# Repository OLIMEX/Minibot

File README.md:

# Minibot
Small Educational Robot programmable with Arduino, with two motors and sensors to follow line or escape from labyrinth

## LICENSE
* Software License is GPL3
* Hardware License is Apache 2.0
* Documentation License is CC-BY-SA3.0 (https://creativecommons.org/licenses/by-sa/3.0/)

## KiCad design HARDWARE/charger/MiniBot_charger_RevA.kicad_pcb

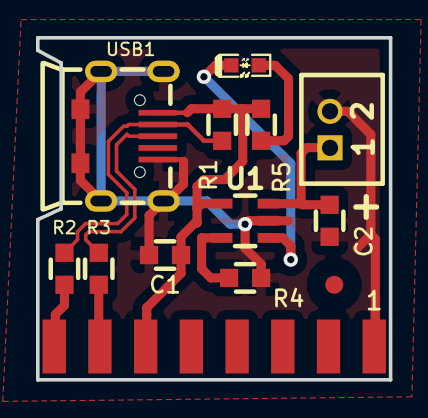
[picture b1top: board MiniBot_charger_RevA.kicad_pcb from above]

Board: 2 copper layers, 19.6 x 19.0 mm, 13 parts (0 on the bottom side), 10 nets.

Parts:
BAT_CON1: BAT_CON; LIPO_BAT_VERTICAL_DW02S
C1, C2: 2.2uF/6.3V; C_0603_5MIL_DWS
CON1: CON8; SIP8_SMD
LED1: LED_Small; LED_0603_KA
R1: 1.5K; R_0603_5MIL_DWS
R2, R3: 22R; R_0603_5MIL_DWS
R4: 13K_1%; R_0603_5MIL_DWS
R5: 10K; R_0603_5MIL_DWS
Ref*: Val**; Fiducial1x3_transp
U1: BL4054B-42TPRN(SOT23-5); SOT-23-5
USB1: USB-uicro; USB-MICRO_MISB-SWMM-5B_LF

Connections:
/D_N: R1.2, R2.2, USB1.2
/D_P: R3.2, USB1.3
GND: BAT_CON1.2, C1.2, C2.2, CON1.1, R4.2, U1.2, USB1.0, USB1.5
unnamed: BAT_CON1.1, C2.1, U1.3
unnamed: C1.1, CON1.6, R1.1, R5.1, U1.4, USB1.1
unnamed: CON1.7, R3.1
unnamed: CON1.8, R2.1
unnamed: LED1.1, U1.1
unnamed: LED1.2, R5.2
unnamed: R4.1, U1.5

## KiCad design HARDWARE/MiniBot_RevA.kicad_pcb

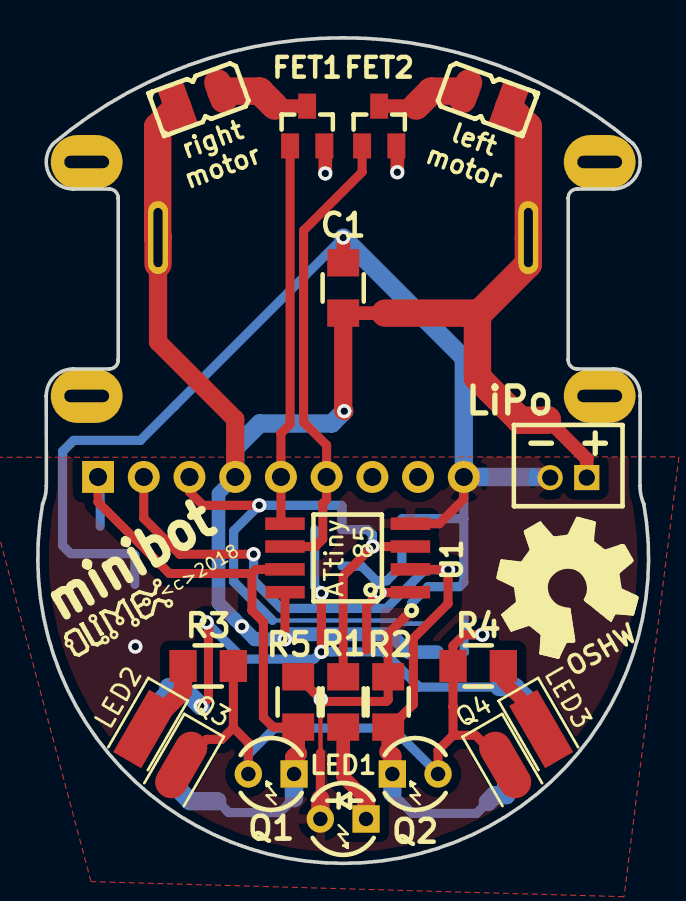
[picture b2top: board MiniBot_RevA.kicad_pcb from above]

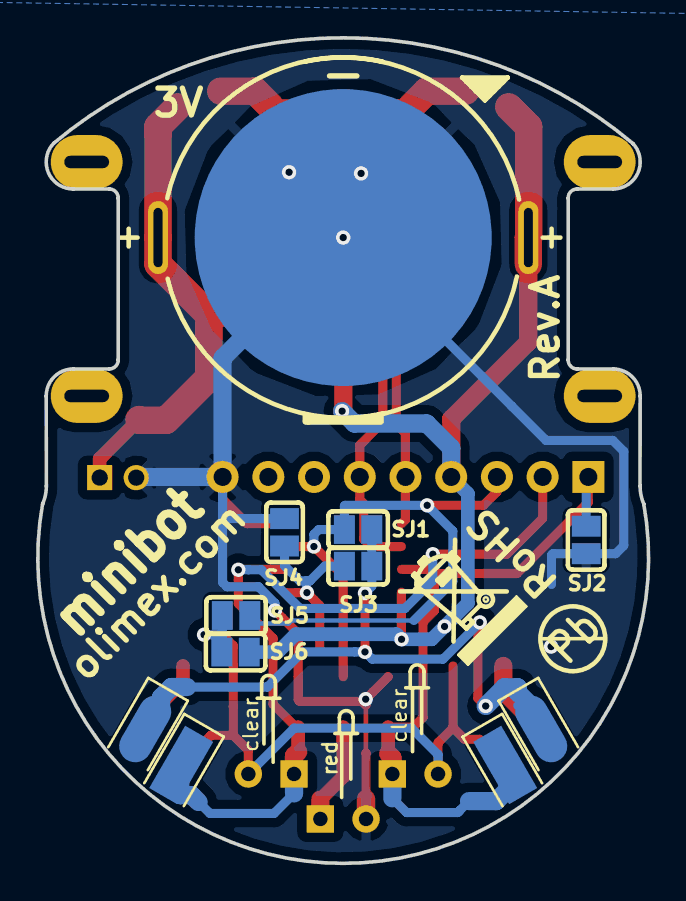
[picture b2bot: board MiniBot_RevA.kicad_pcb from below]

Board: 2 copper layers, 33.9 x 45.9 mm, 27 parts (7 on the bottom side), 15 nets.

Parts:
BAT1: Battery; CR2032H_PTH
BAT_CON2: BAT_CON; LIPO_BAT_VERTICAL_DW02S
C1: C_Small; C_1206_5MIL_DWS
CON1: LEFT MOTOR; MIC-TERES
CON2: RIGHT MOTOR; MIC-TERES
EXT1: nRF; HN1x9
FET1, FET2: WNM2016-3; SOT23
LED1: RED 3mm; LED-3mm-PTH-KA
LED2, LED3: RED 3mm; LED-EDGE
Q1, Q2: L342; LED-3mm-PTH-KA
Q3, Q4: L342; L34x-EDGE
R1, R3, R4: 1K; R_1206_5MIL_DWS
R2, R5: 3.3K; R_1206_5MIL_DWS
SJ1: leds_join; SJ
SJ2: arduino; SJ
SJ3, SJ5, SJ6: eco; SJ
SJ4: reset; SJ
U1: ATTINY85-20PU; SO-8_208mil

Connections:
/BAT+: BAT1.1, BAT_CON2.1, C1.1, CON1.1, CON2.1, EXT1.4, SJ6.2, U1.8
/FLED: SJ3.1, SJ4.1, U1.1
/LMOTOR: EXT1.6, FET2.1, U1.6
/LSENSE: EXT1.2, Q2.1, Q4.1, R2.1, U1.2
/RMOTOR: EXT1.5, FET1.1, U1.5
/RSENSE: EXT1.1, Q1.1, Q3.1, R5.1, SJ2.2, U1.7
/SLED: EXT1.3, R1.1, SJ1.1, SJ5.2, U1.3
GND: BAT1.2, BAT_CON2.2, C1.2, EXT1.9, FET1.2, FET2.2, LED1.1, R2.2, R5.2, SJ2.1, SJ4.2, U1.4
unnamed: CON1.2, FET2.3
unnamed: CON2.2, FET1.3
unnamed: LED1.2, R1.2
unnamed: LED2.1, LED3.1, SJ1.2, SJ3.2
unnamed: LED2.2, R3.2
unnamed: LED3.2, R4.2
unnamed: Q1.2, Q2.2, Q3.2, Q4.2, R3.1, R4.1, SJ5.1, SJ6.1

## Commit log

2019-06-11 Initial
2025-01-31 Update
    New version of manual release
